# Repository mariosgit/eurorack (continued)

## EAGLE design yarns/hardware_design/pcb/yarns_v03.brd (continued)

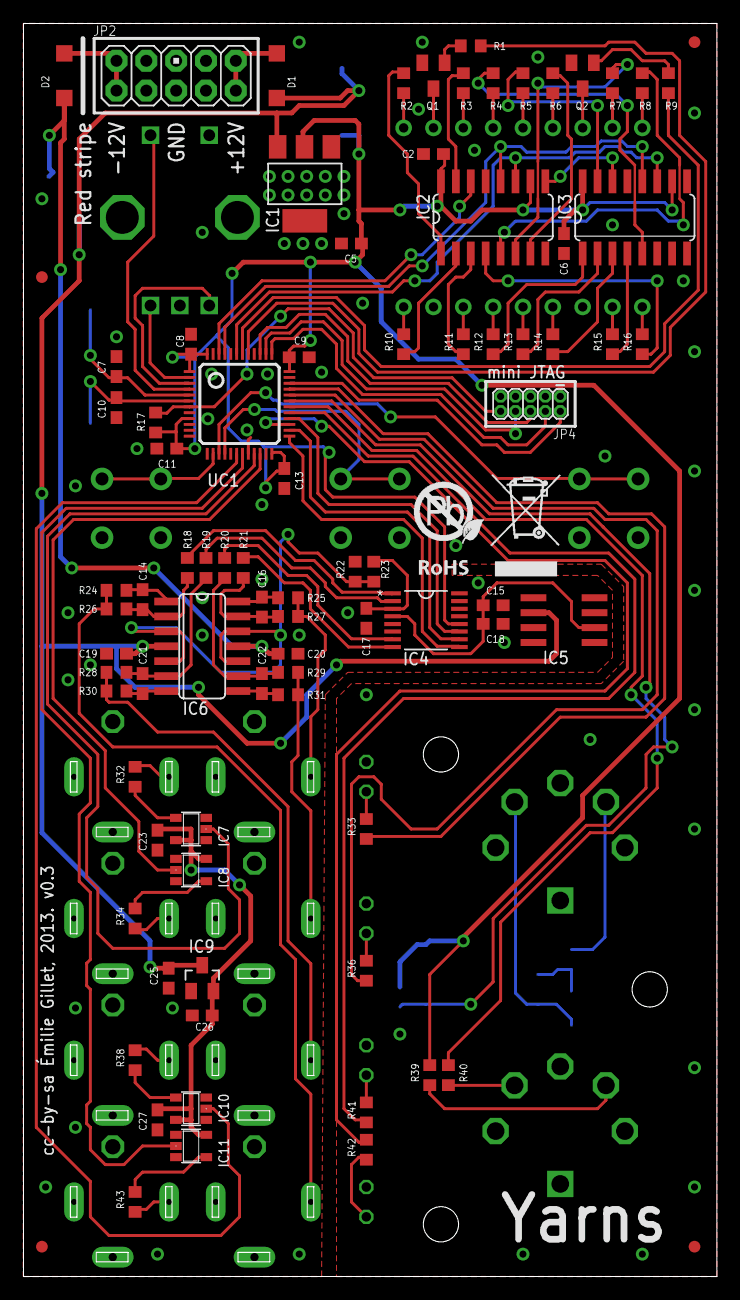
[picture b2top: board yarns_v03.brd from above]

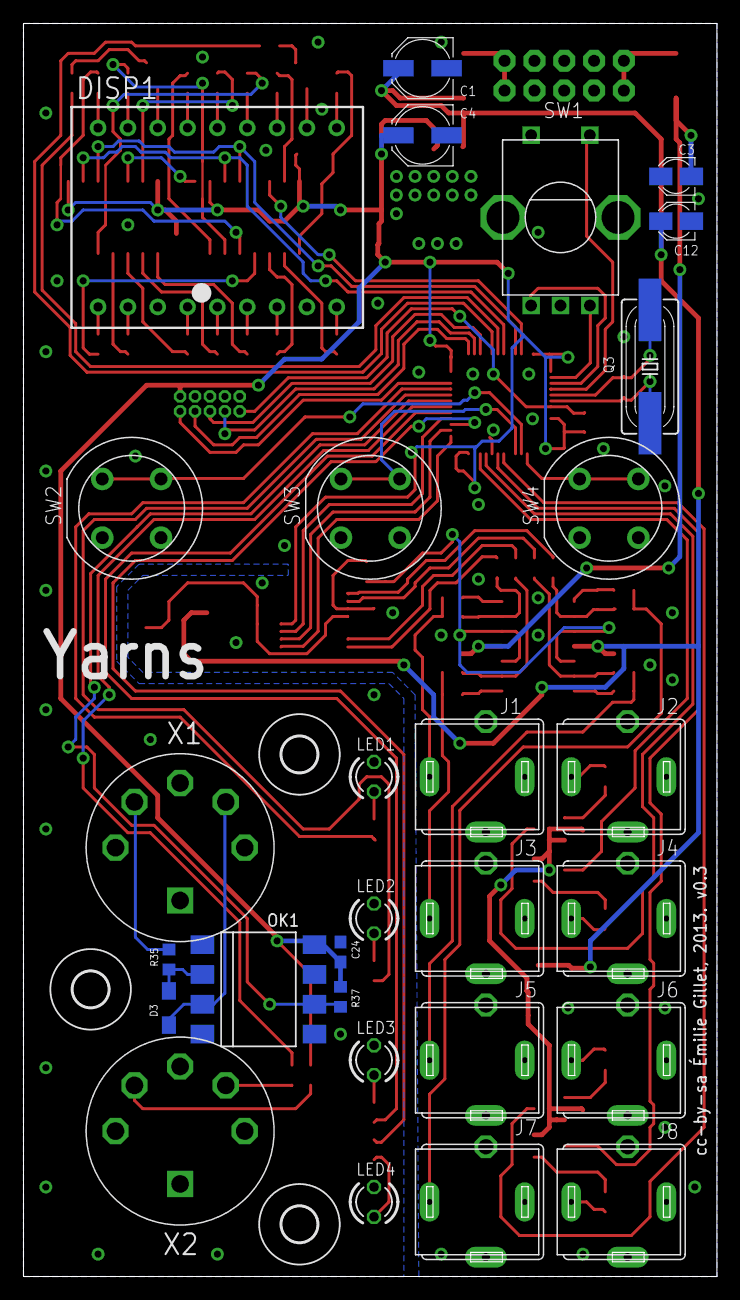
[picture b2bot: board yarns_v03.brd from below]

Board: 2 copper layers, 59.0 x 106.7 mm, 118 parts (32 on the bottom side), 107 nets.

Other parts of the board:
U$2, U$3, U$4: 3,0
U$5: ROHS

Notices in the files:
yarns/hardware_design/pcb/yarns_v03.brd:
cc-by-sa Émilie Gillet, 2013. v0.3
